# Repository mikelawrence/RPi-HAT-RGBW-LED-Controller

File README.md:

# Raspberry Pi RGBW LED Controller HAT
This is a [Raspberry Pi B+ HAT](https://github.com/raspberrypi/hats) that supports four high power LEDs. Each LED output uses a resistor configurable constant current driver with PWM support to control light intensity. A fourth LED channel was added to support color LEDs that have an extra Green or White LED. This HAT also supports Common-Anode LED configurations. The component selection as shown in the BOM is for a 50W RGB LED light that uses a constant current of 550mA at 24V-16.8V. The Design section discusses this in detail.

This PCB is designed using [KiCad 5.0.0](http://kicad.org). This HAT is based on [RPi_Hat_Template](https://github.com/xesscorp/RPi_Hat_Template) by XESS Corp.

_Note: The LM3414 parts have an exposed pad on the bottom which requires either a reflow oven or hot air to solder properly._

_Note: This HAT does not have the camera flex slot or the display flex cutout so technically cannot be called a HAT._

## Status
* Rev 1.0 PCB has been ordered, assembled, and tested.
  * Order the PCB from [OSH Park](https://oshpark.com/shared_projects/8nXTFx94).
  * Order the parts from Mouser using this [Shared BOM](https://www.mouser.com/ProjectManager/ProjectDetail.aspx?AccessID=8e67d22b4b).
  * The Green LED failed on one of my lights. The board is working as it should. This is most likely a LED module problem or incorrect output current. Replaced the module, changed the current from 550mA to 500mA and added a scale factor on the green output which currently limits the duty cycle to a maximum of 75%. Green output is higher in intensity anyways.

## Board Preview

## Design
### Input Power
Input power is 36VDC nominal with a range of 30V-37V. Input current is a maximum of 2A. This limit is due to the maximum current of the reverse input protection bridge rectifier (D1) which also serves to reduce the voltage on the 5V DC-DC converter (U3). If higher current is needed remove D1 and make the maximum input voltage 35VDC.

The Raspberry Pi can be safely back-powered by this HAT because the Ideal Diode circuit provides protection to both the Raspberry Pi and this HAT when the Raspberry Pi is powered by another source. Maximum Raspberry Pi power is 1.5A. Usually the Raspberry Pi will take substantially less than 1.5A when it is used with no external connections.

Example power budget...Powering a [50W RGB LED light](http://www.ebay.com/sch/sis.html?_nkw=Floodoor+LED+RGB+Flood+Light50W+Outdoor+Lights+Spot+Light+Lanscape+Lighting+w...&_id=253049210560&&_trksid=p2060353.m2749.l2658) purchased on eBay. The RGB LEDs of this light are wired with four wires in a common-anode configuration. For this light the White LED section is left unpopulated.

|                           | Current | Voltage | Power |
|---------------------------|---------|---------|-------|
| Red                       | 550mA   | 16.8V   | 9.24W |
| Green                     | 550mA   | 24V     | 13.2W |
| Blue                      | 550mA   | 24V     | 13.2W |
| LED Power                 |         |         | 35.6W |
| LED Power @ 80% Efficiency|         |         | 44.6W |
| Raspberry Pi              |         |         | 10.0W |
| Total System Power        |         |         | 54.6W |

A 60W 36VDC power supply will drive the Raspberry Pi, RGBW LED Controller HAT, and the High Power LEDs. [This](http://www.meanwellusa.com/webapp/product/search.aspx?prod=HLG-60H) power supply (part number HLG-60) from Mean Well will drive the 50W RGB light nicely.

### Power Reality Check
In my testing I placed a Raspberry Pi, RGBW LED Controller HAT, and a 60W Power Supply in an enclosure to check temperatures. When I ran a rainbow sweep test the power consumption was around 18W and the HAT had a temperature rise of about 20C - 25C over room temperature. A static purple color test (both read and blue at full power) with power consumption around 35W the HAT temperature rise was 30C - 35C. Clearly this HAT will need better cooling to run higher power LED configurations.

### LED driver
The LM3414 from TI is a 1-A, 60-W Common Anode-Capable Constant Current Buck LED Driver. Most constant current LED drivers have a current sense resistor in the high-side path which prevents common anode connections. The LM3414 puts the current sense resistor on the low side. This leaves the high side connected directly to the 36V of the input power. The positive side of all four LED outputs are connected together on the board forcing a common-anode topology. You must not connect the low side to ground.

The LM3414 average LED current (I<sub>L</sub>) is set by the R<sub>IADJ</sub> (R7, R9, R11, R13). Set LED average current to 550mA using the equation below.

Using the standard 1% resistor value the average LED current is

Choose a standard switching frequency (f<sub>SW</sub>) of 500kHz using equation below. Switching frequency (f<sub>SW</sub>) is set by R<sub>FS</sub> (R6, R8, R10, R12).

Using the standard 1% resistor value the switching frequency is

Determine minimum inductor value from maximum peak-to-peak LED current ripple (ΔI<sub>LPP</sub>) using equation below. Set ΔI<sub>LPP</sub> to 200mA.

Using the standard inductor value the peak-to-peak LED current ripple is

Determine peak LED current (I<sub>LP</sub>) using selected components using equation below. I<sub>LP</sub> is also the peak current through the inductor.

Compute the operating duty cycle (D) using equation below.

Determine minimum C<sub>IN</sub> (C7, C9, C11, C13) for 200mV or less voltage ripple (ΔV<sub>IN</sub>) using equation below.

### PWM Controller
A Raspberry Pi has only one hardware capable PWM pin (GPIO18). With up to four PWM outputs needed for this HAT I decided to use a PCA9685 from NXP alleviate the load on the Raspberry Pi. The PCA9685 from NXP is a 16-Channel, 12-bit, I<sup>2</sup>C PWM controller. It supports independent LED on and off times so the LED outputs can be adjusted in phase along with pulse width. However, when phase is changed from 0 the next PWM cycle will reset the output. For frequent updates this causes the output light to flicker.

There are few settings that are important to using the PCA9685 on this HAT. First the EXTCLK bit in the MODE1 register must be set to 0. In the MODE2 register the INVRT bit must be set to 0 and the OUTDRV bit must be set to 1. Luckily this is the default state for all of these bits.

## Raspberry Pi Setup
This setup makes two key assumptions. First you are using Raspbian. Second, Python3 is the target programming environment. Install or update Python3 and necessary libraries by performing the following...
```
sudo apt-get update
sudo apt-get -y install build-essential python3-dev python3-pip git i2c-tools python3-w1thermsensor
pip3 install Adafruit-GPIO paho-mqtt
```

### Clone this Repository
Now is a good time to clone this repository on your Raspberry Pi. Clearly the KiCad files are not needed to configure and run this code on your Raspberry Pi so you pick and choose the files needed but these instructions will clone the entire repository.
```
mkdir ~/projects
cd ~/projects
git clone https://github.com/mikelawrence/RPi-HAT-RGBW-LED-Controller
```

### Configure ID EEPROM
Raspberry Pi HATs require an ID EEPROM with data that uniquely identifies every hat ever made. Start by cloning this repository on your Raspberry Pi, building the EEPROM tools, and make the the `eeprom_settings.eep` file.
```
cd ~/projects/RPi-HAT-RGBW-LED-Controller/eeprom/
make all
./eepmake eeprom_settings.txt eeprom_settings.eep
```
The next command writes the freshly generated and unique `eeprom_settings.eep` file to the EEPROM but you must push and hold the write switch on the HAT before executing this command. By default the EEPROM on the HAT is write protected. Pushing the write switch allows writes to occur.
```
sudo ./eepflash.sh -w -f=eeprom_settings.eep -t=24c32
```
You will see the following if writing to the EEPROM was successful.
```
This will attempt to talk to an eeprom at i2c address 0x50. Make sure there is an eeprom at this address.
This script comes with ABSOLUTELY no warranty. Continue only if you know what you are doing.
Do you wish to continue? (yes/no): yes
Writing...
0+1 records in
0+1 records out
117 bytes (117 B) copied, 2.31931 s, 0.1 kB/s
Done.
```
This is what you will see if there is a problem communicating with the EEPROM.
```
This will attempt to talk to an eeprom at i2c address 0x50. Make sure there is an eeprom at this address.
This script comes with ABSOLUTELY no warranty. Continue only if you know what you are doing.
Do you wish to continue? (yes/no): yes
Writing...
dd: error writing ‘/sys/class/i2c-adapter/i2c-3/3-0050/eeprom’: Connection timed out
0+1 records in
0+0 records out
0 bytes (0 B) copied, 0.0539977 s, 0.0 kB/s
Error doing I/O operation.
```

### Setup Interfaces
For this HAT you will need to enable the I<sup>2</sup>C and 1-Wire interfaces. From the command line type `sudo raspi-config ` and follow the prompts to install I<sup>2</sup>C support in the kernel.

Now follow the same actions but enabling the 1-Wire interface.

It's time to reboot your Raspberry Pi with `sudo reboot`.

### Test PCA9685 12-bit PWM Controller
Now let's see if the PWM Controller is present on the I<sup>2</sup>C bus by running `sudo i2cdetect -y 1`. Looking at the output of the `i2cdetect` command you will see `40` and `70` in a field of `--` when the PCA9685 is detected on the bus. If you don't see the `40` something is wrong with the HAT or the bus is disabled. `i2cdetect` was installed when you installed the i2c-tools package in the Raspberry Pi Setup section.
```
pi@rpi-rgb-led-1:~ $ sudo i2cdetect -y 1
     0  1  2  3  4  5  6  7  8  9  a  b  c  d  e  f
00:          -- -- -- -- -- -- -- -- -- -- -- -- --
10: -- -- -- -- -- -- -- -- -- -- -- -- -- -- -- --
20: -- -- -- -- -- -- -- -- -- -- -- -- -- -- -- --
30: -- -- -- -- -- -- -- -- -- -- -- -- -- -- -- --
40: 40 -- -- -- -- -- -- -- -- -- -- -- -- -- -- --
50: -- -- -- -- -- -- -- -- -- -- -- -- -- -- -- --
60: -- -- -- -- -- -- -- -- -- -- -- -- -- -- -- --
70: 70 -- -- -- -- -- -- --                         
```

### Test the DS18B20 1-Wire Thermometer
[Python3-w1thermsensor](https://github.com/timofurrer/w1thermsensor) is a nice 1-Wire python library that also supports command line reading of temperatures from 1-Wire devices. You should have already installed this package in the [Raspberry Pi Setup](#Raspberry-Pi-Setup) section.

Now test the RGBW LED Controller HAT's DS18B20 temperature sensor using `w1thermsensor all`.
```
pi@rpi-rgb-led-1:~ $ w1thermsensor all
Got temperatures of 1 sensors:
  Sensor 1 (00000991f822) measured temperature: 25.69 celsius
```
# RGBW LED Controller HAT Test
See code-test section [README.md](code-test/README.md) for code that fires up the RGBW LED Controller HAT by blending between the primary colors and monitoring temperatures.

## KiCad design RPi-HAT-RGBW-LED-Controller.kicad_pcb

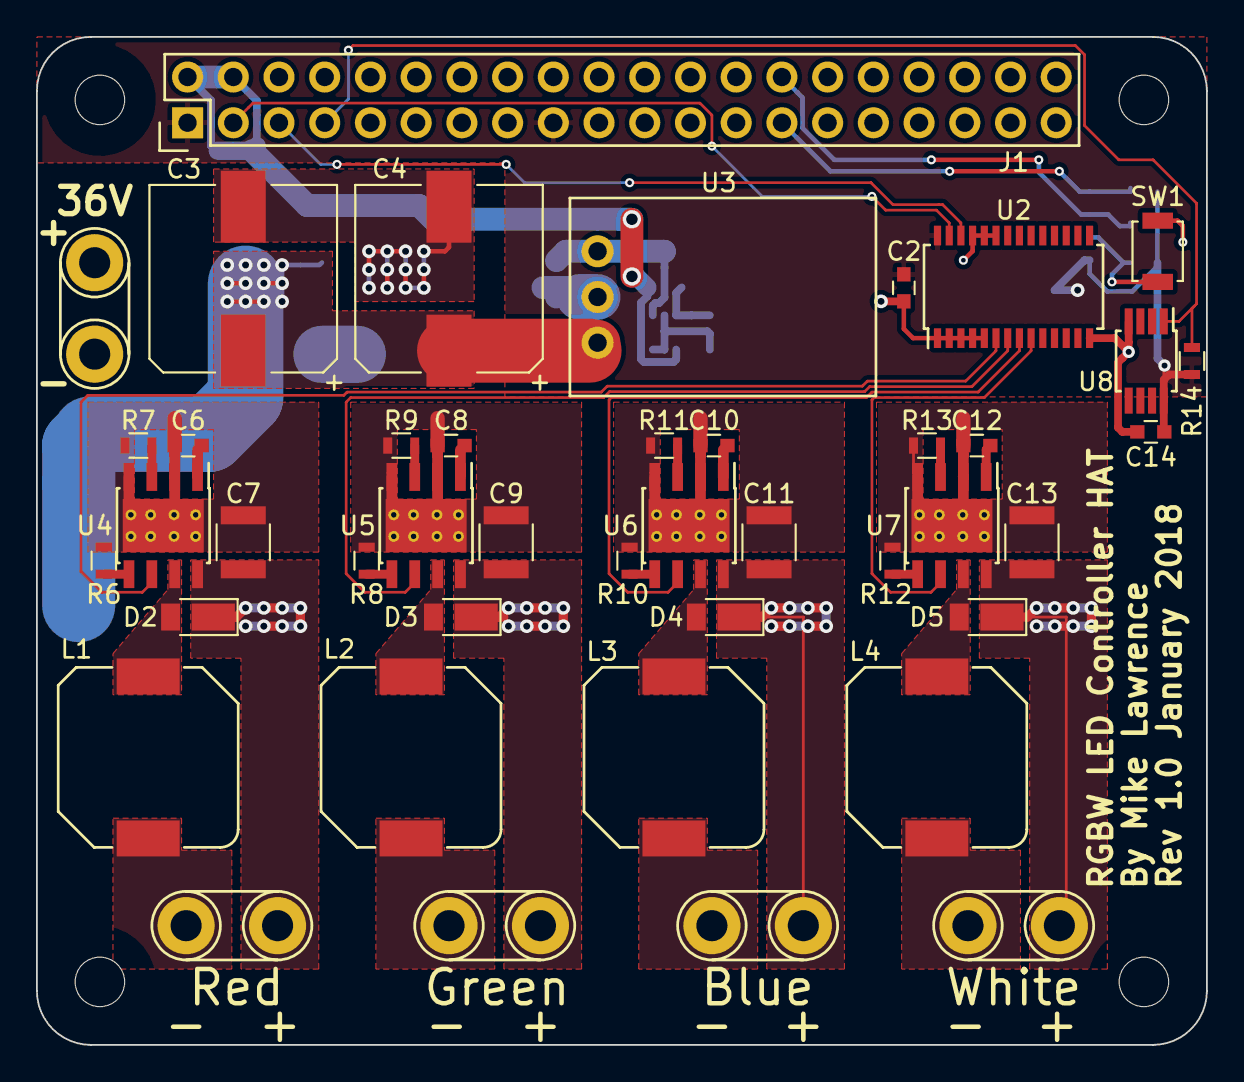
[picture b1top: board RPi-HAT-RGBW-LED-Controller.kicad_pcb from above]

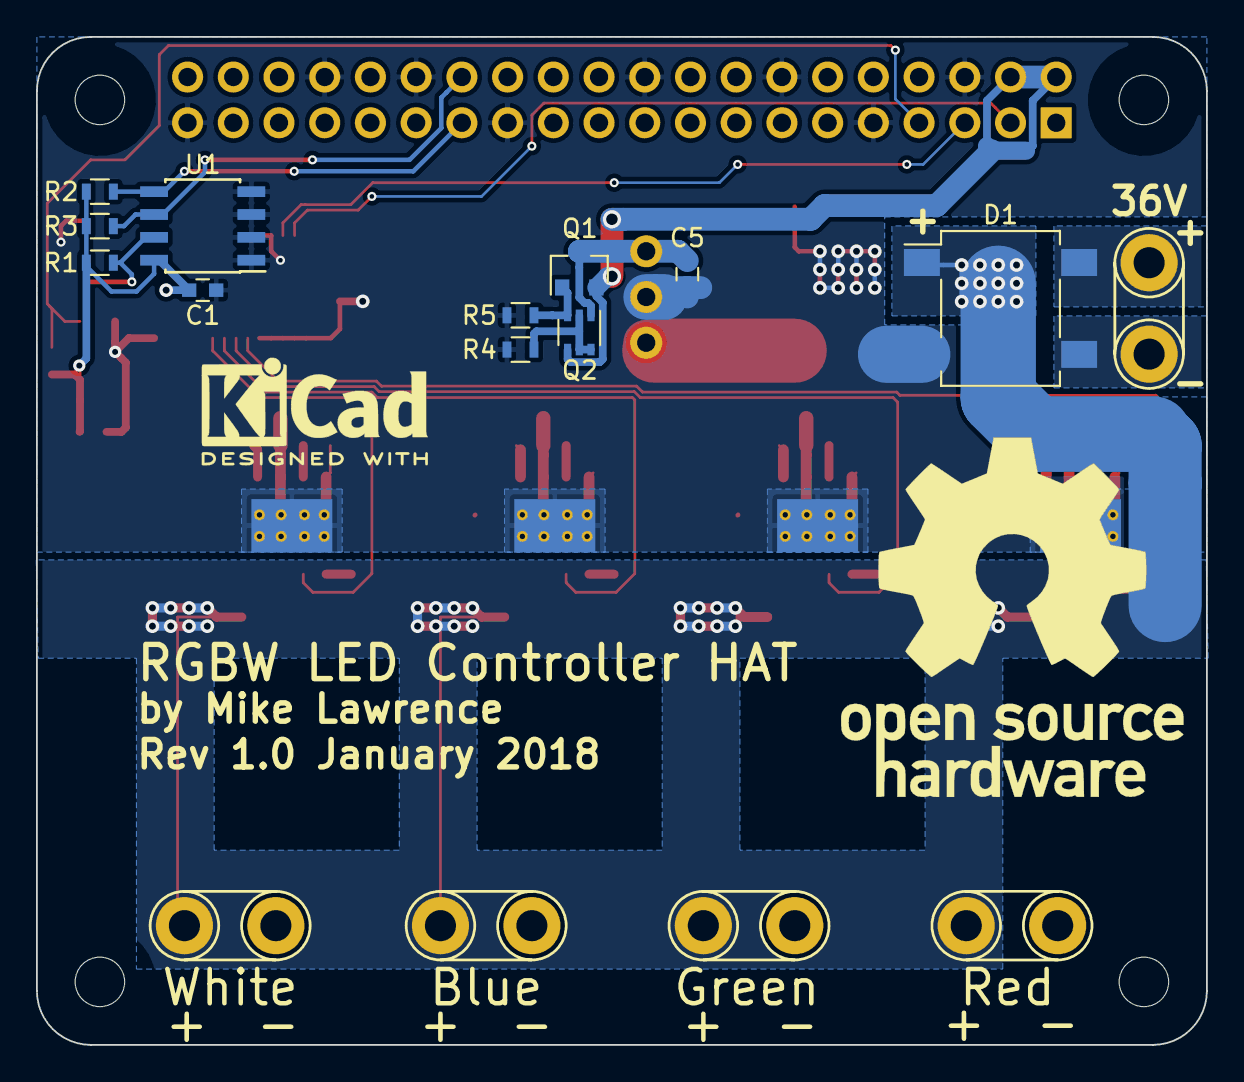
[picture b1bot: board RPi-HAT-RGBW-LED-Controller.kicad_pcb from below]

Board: 2 copper layers, 65.0 x 56.0 mm, 54 parts (11 on the bottom side), 39 nets.

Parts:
C1, C2, C14: 0.1uF; C_0603
C3, C4: 330uF; CP_Elec_10x10.5
C5, C6, C8, C10, C12: 1uF; C_0603
C7, C9, C11, C13: 2.2uF; C_1210
D1: D_Bridge_+-AA; Diode_Bridge_DFS
D2, D3, D4, D5: DFLS2100; D_PowerDI-123
J1: RPi_GPIO; Pin_Header_Straight_2x20
J2, J3, J4, J5, J6: Conn_01x02_Female; TH_16ga_2pos
L1, L2, L3, L4: 100uH; WE-PD-1050
Q1: DMG2305UX; SOT-23
Q2: BCM857BS; SOT-363_SC-70-6
R1: 1k; R_0603
R2, R3: 3.9k; R_0603
R4: 10k; R_0603
R5: 47k; R_0603
R6, R8, R10, R12: 40.2k; R_0603
R7, R9, R11, R13: 5.76k; R_0603
R14: 4.7k; R_0603
SW1: Write; SW_SPST_B3U-1000P
U1: AT24CS32; SOIC-8_3.9x4.9mm_Pitch1.27mm
U2: PCA9685; TSSOP-28_4.4x9.7mm_Pitch0.65mm
U3: OKI-78SR-5; 78SR-H
U4, U5, U6, U7: LM3414; TI_SO-PowerPAD-8_ThermalVias
U8: DS18B20U; MSOP-8_3x3mm_Pitch0.65mm

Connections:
+3V3: C1.1, C2.1, C14.1, J1.1, J1.17, R1.1, R2.1, R3.1, R14.1, U1.8, U2.28, U8.8
+5V: J1.2, J1.4, Q1.2, Q2.4
+5VP: C5.1, Q1.3, Q2.1, U3.3
+VDC: C3.1, C4.1, C7.1, C9.1, C11.1, C13.1, D1.1, D2.1, D3.1, D4.1, D5.1, J3.1, J4.1, J5.1, J6.1, U3.1, U4.8, U5.8, U6.8, U7.8
/-B: J5.2, L3.2
/-G: J4.2, L2.2
/-R: J3.2, L1.2
/-W: J6.2, L4.2
/ID_SC: J1.28, R3.2, U1.6
/ID_SD: J1.27, R2.2, U1.5
/LXB: D4.2, L3.1, U6.7
/LXG: D3.2, L2.1, U5.7
/LXR: D2.2, L1.1, U4.7
/LXW: D5.2, L4.1, U7.7
/SCL: J1.5, U2.26
/SDA: J1.3, U2.27
/VinA: D1.3, J2.1
/VinB: D1.4, J2.2
GND: C1.2, C2.2, C3.2, C4.2, C5.2, C6.2, C7.2, C8.2, C9.2, C10.2, C11.2, C12.2, C13.2, C14.2, D1.2, J1.6, J1.9, J1.14, J1.20, J1.25, J1.30, J1.34, J1.39, R4.2, R5.2, R6.1, R7.1, R8.1, R9.1, R10.1, R11.1, R12.1, R13.1, SW1.2, U1.1, U1.2, U1.3, U1.4, U2.1, U2.2, U2.3, U2.4, U2.5, U2.14, U2.23, U2.24, U2.25, U3.2, U4.2, U4.4, U4.9, U5.2, U5.4, U5.9, U6.2, U6.4, U6.9, U7.2, U7.4, U7.9, U8.4
unnamed: C6.1, U4.1
unnamed: C8.1, U5.1
unnamed: C10.1, U6.1
unnamed: C12.1, U7.1
unnamed: Q1.1, Q2.3, R5.1
unnamed: Q2.2, Q2.5, Q2.6, R4.1
unnamed: R1.2, SW1.1, U1.7
unnamed: R6.2, U4.5
unnamed: R7.2, U4.3
unnamed: R8.2, U5.5
unnamed: R9.2, U5.3
unnamed: R10.2, U6.5
unnamed: R11.2, U6.3
unnamed: R12.2, U7.5
unnamed: R13.2, U7.3
unnamed: U2.6, U4.6
unnamed: U2.7, U5.6
unnamed: U2.8, U6.6
unnamed: U2.9, U7.6
OW: J1.7, R14.2, U8.1

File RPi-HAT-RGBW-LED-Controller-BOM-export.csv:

Reference, Quantity, Value, Footprint, Datasheet, Part Number, Manufacturer, Vendor, Vendor Part Number, Tolerance, Voltage
C1 C14 C2 ,3,"0.1uF","Capacitors_SMD:C_0603","","GCJ188R71E104KA2D","Murata","Mouser","81-GCJ188R71E104KA2D","10%","25V"
C3 C4 ,2,"330uF","Capacitors_SMD:CP_Elec_10x10.5","","EEE-FT1H331GP","Panasonic","Mouser","667-EEE-FT1H331GP","20%","50V"
C10 C12 C5 C6 C8 ,5,"1uF","Capacitors_SMD:C_0603","","GCJ188R71E105KA01D","Murata","Mouser","81-GCJ188R71E105KA1D","10%","25V"
C11 C13 C7 C9 ,4,"2.2uF","Capacitors_SMD:C_1210","","GCJ32DR72A225KA01L","Murata","Mouser","81-GCJ32DR72A225KA1L","10%","100V"
D1 ,1,"D_Bridge_+-AA","Diodes_SMD:Diode_Bridge_DFS","https://www.mouser.com/ds/2/80/DF2005S-G%20Thru340567.%20DF2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","DF206ST-G","Comchip Tech","Mouser","750-DF206ST-G","",""
D2 D3 D4 D5 ,4,"DFLS2100","Diodes_SMD:D_PowerDI-123","https://www.diodes.com/assets/Datasheets/ds31475.pdf","DFLS2100-7","Diodes Inc","Mouser","621-DFLS2100-7","",""
J1 ,1,"RPi_GPIO","raspberry-ml:Pin_Header_Straight_2x20","","2222","Adafruit","Mouser","485-2222","",""
J2 J3 J4 J5 J6 ,5,"Conn_01x02_Female","holes-ml:TH_16ga_2pos",""
L1 L2 L3 L4 ,4,"100uH","inductors-ml:WE-PD-1050","","7447714101","Wurth","Mouser","710-7447714101","",""
Q1 ,1,"DMG2305UX","TO_SOT_Packages_SMD:SOT-23","https://www.diodes.com/assets/Datasheets/DMG2305UX.pdf","DMG2305UX-7","Diodes Inc","Mouser","621-DMG2305UX-7","",""
Q2 ,1,"BCM857BS","TO_SOT_Packages_SMD:SOT-363_SC-70-6","https://www.diodes.com/assets/Datasheets/BCM857BS.pdf","BCM857BS-7-F","Diodes Inc","Mouser","621-BCM857BS-7-F","",""
R1 ,1,"1k","Resistors_SMD:R_0603","","ERJ-3EKF1001V","Panasonic","Mouser","667-ERJ-3EKF1001V","1%",""
R14 ,1,"4.7k","Resistors_SMD:R_0603","","ERJ-3EKF4701V","Panasonic","Mouser","667-ERJ-3EKF4701V","1%",""
R2 R3 ,2,"3.9k","Resistors_SMD:R_0603","","ERJ-3EKF3901V","Panasonic","Mouser","667-ERJ-3EKF3901V","1%",""
R4 ,1,"10k","Resistors_SMD:R_0603","","ERJ-3EKF1002V","Panasonic","Mouser","667-ERJ-3EKF1002V","1%",""
R5 ,1,"47k","Resistors_SMD:R_0603","","ERJ-3EKF4702V","Panasonic","Mouser","667-ERJ-3EKF4702V","1%",""
R10 R12 R6 R8 ,4,"40.2k","Resistors_SMD:R_0603","","ERJ-3EKF4022V","Panasonic","Mouser","667-ERJ-3EKF4022V","1%",""
R11 R13 R7 R9 ,4,"5.76k","Resistors_SMD:R_0603","","ERJ-3EKF5761V","Panasonic","Mouser","667-ERJ-3EKF5761V","1%",""
SW1 ,1,"Write","Buttons_Switches_SMD:SW_SPST_B3U-1000P","http://www.mouser.com/ds/2/307/en-b3u-3615.pdf","B3U-1000P","Omron","Mouser","653-B3U-1000P","",""
U1 ,1,"AT24CS32","Housings_SOIC:SOIC-8_3.9x4.9mm_Pitch1.27mm","http://www.atmel.com/images/Atmel-8869-SEEPROM-AT24CS32-Data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","AT24CS32-SSHM","Atmel","Mouser","556-AT24CS32-SSHM-T","",""
U2 ,1,"PCA9685","Housings_SSOP:TSSOP-28_4.4x9.7mm_Pitch0.65mm","","PCA9685PW","NXP","Mouser","771-PCA9685PW,112","",""
U3 ,1,"OKI-78SR-5","murata-ml:78SR-H","","OKI-78SR-5/1.5-W36H-C","Murata","Mouser","580-OKI78SR51.5W36HC","",""
U4 U5 U6 U7 ,4,"LM3414","Housings_SOIC:TI_SO-PowerPAD-8_ThermalVias","","LM3414MRX/NOPB","TI","Mouser","926-LM3414MRX/NOPB","",""
U8 ,1,"DS18B20U","Housings_SSOP:MSOP-8_3x3mm_Pitch0.65mm","https://datasheets.maximintegrated.com/en/ds/DS18B20.pdf","DS18B20U+","Maxim","Mouser","700-DS18B20U","",""

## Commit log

2018-01-27 Fix Board Preview
2018-01-27 Fix DS18B20
2018-02-02 Minor corrections
2018-02-10 Minor changes to README's
2018-02-10 Add LICENSE file
2018-02-10 Another minor fix to README
2018-02-10 Add code-light section
    Added application to support RGB Floodlight and Home Assistant
2018-02-10 Minor fixes to README
2018-02-21 Removed unnecessary state file.
    This file is created on the fly.
2018-02-21 PEP 8 and minor comment edits
2018-02-21 Minor edits
2018-02-21 PEP 8
2018-02-21 PEP 8 and make availability configurable
2018-05-14 Remove RGB and flood from names in config file.
2018-05-15 Added RGB scaling that will limit maximum duty cycle for each color. Updated status.
2018-05-31 Fix max temperature algorithm. Fixed mistake in Home Assistant yaml configuration in README.
2018-06-03 Added RSSI sensor to MQTT. Handle initial MQTT connect better.
    MQTT connect now looks for exceptions and will retry forever until connected. Replaces dashes in Node_ID and Group_ID with underscores. Home Assistant automatically replaces dashes and other special 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
2018-07-24 Upgrade to KiCad 5.0.0. Remove necessary files.
2018-11-04 Update README's and change Halloween colors.
2018-11-04 More README updates.
2018-12-04 Removed publish blank group topic.
    Caused the group light to go away depending on boot order of lights in a group.
2019-01-05 Support Home Assistant MQTT light JSON schema change.
2019-01-05 Changed README's to make cloning this repository clearer.
2019-06-28 Added MQTT authentication and improved availability for Home Assistant.
    Added MQTT username and password authentication.
    Better support for Home Assistant availabilty.
    Changed to Home Assistant MQTT discovery abbreviations.
    MQTT QOS is now defined in one place.
    Fix configuration defaults in configparser.
2020-02-04 Add better Home Assistant Discovery support
2021-11-08 Update Kicad link.
